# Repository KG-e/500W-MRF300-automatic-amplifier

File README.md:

# 500W-MRF300-automatic-amplifier

A fully automatic 500 W HF amateur radio amplifier (3.5–28 MHz) using a push-pull MRF300 LDMOS output stage with transmission-line transformers (TLTs). The amplifier automatically measures operating frequency, selects the appropriate low-pass filter, adjusts input drive power, monitors protection systems, and includes an automatic antenna tuner and touchscreen HMI.

**Author:** S56KG (https://www.qrz.com/db/S56KG)
This was a final-year high school project (slovenian "tehnična poklicna matura")

---

## Overview

Commercial automatic HF amplifiers with equivalent specs typically cost **3,000–5,000€**. This project was set out to build a comparable **500W HF amplifier** - with automatic band switching, automatic input leveling (attenuator), and full protection circuitry - for half the price (built for ~1,500€ including six output transistors lost to testing mishaps; a second build would cost roughly **1,300€**).

Unlike most homebrew amplifiers, the goal here was full automation: no manual band switching, no manual tuning sequence - just key up and go.

## Key Features

- **Fully automatic operation** - no manual warm-up/tuning procedure required
- **Automatic input attenuator** with power measurement, stepping through 0.5–6 dB stages to hit an ideal ~4W drive level
- **Push-pull output stage** using 2× MRF300 LDMOS transistors, up to ~530W PEP, depending on freq.
- **Automatic low-pass filter selection** based on measured carrier frequency (LPF harmonics are ≤ −65 dBc)
- **Dual-MCU architecture** (2× ATmega2560) communicating over UART, with a custom protocol (type-checked, range-checked, heartbeat-monitored)
- **Nextion touchscreen HMI** showing forward/reflected power, SWR, current, temperature, state, band, gain, and losses in real time
- **Full protection**: overcurrent shutdown (soft-latched via SET-RESET logic), SWR protection, thermal protection, bias monitoring
- **Built-in antenna tuner board** (7x7 L-network, based on the N7DDC ATU-100 topology) - hardware complete, control algorithm in testing
- Extra feature connectors for future interfacing (not yet made PC digital control using a PiPico server) 
- Backup analog voltage/current meter on the front panel

## Design Goals

- At least 450W output
- Fully automatic operation without manual tuning
- Comprehensive protection for the MRF300 output devices 
- Support contest-style rapid TX/RX switching
- Maintain harmonic suppression below −65 dBc
- Operate from 3.5–28 MHz with automatic band detection
- Provide a commercial-style touchscreen HMI for all key operational values
- Build using only readily available components on DigiKey

## How It Works

**Transmit state machine:** `INIT → WAIT → FIRST START → INPUT SETUP → LOW POWER TX → TX SWITCH → HIGH POWER TX → READY`. The "ready" state remembers the last transmission and skips most of the setup sequence on the next key-up for faster switching, useful for competition use.

## Power/SWR Measurement

Power and SWR are measured using a **tandem match coupler**, rather than a simple directional coupler, since directional couplers perform poorly at low freq. HF. Two transformers (current and voltage) are summed/negated to separate forward and reflected power. Each direction feeds an **AD8310** logarithmic RF power detector (for accuracy across a wide dynamic range, from milliwatts to hundreds of watts), digitized by two 16-bit **ADS1115** ADCs over I2C.

## Boards 
| 1 | Attenuator board | Auto input attenuator (relay-switched, 0.5–6 dB stages, 8 stage), input power/SWR meter, built-in 50ohm dummy load 

| 2 | MCU board | Carrier board for ATmega2560 + ATmega16U2 (Arduino Mega-derived); one per controller 

| 3 | Amplifier board | Push-pull 2× MRF300 output stage, TLT output transformers, high-side current sensing, hardware overcurrent latch 

| 4 | Filter board | Output power/SWR metering + auto-selected low-pass filters (designed in AADE Filter Design + LTspice) 

| 5 | Tuner board | 7x7 L-network automatic antenna tuner (hardware complete, not yet enabled) 

| 6 | Motherboard | MCU carrier, per-board regulated supplies, fan control (6× PWM), 2× ADS1115 ADC, buzzer, overcurrent sensing 

| 7 | Input board | RX/TX switching (opto-isolated relay drive), 50V enable, frequency counter 

All boards are 4-layer FR4 (except the tuner board, 2-layer), designed with trace impedance calculated per JLCPCB dielectric specs.

## Firmware

- Two **ATmega2560** microcontrollers, split because driving the Nextion HMI alone slows a single loop to >30ms. This separates time-critical amplifier control from the touchscreen interface to guarantee deterministic protection response.
  - **Primary MCU**: runs the amplifier state machine, controls the amp stage, PSU, RF switching, attenuator, and filters; measures frequency and enforces fast protection (SWR, current, voltage) every loop.
  - **Secondary MCU**: reads temperature/voltage sensors, drives cooling fans, and manages the Nextion HMI.
- Custom UART protocol between the two MCUs with type checking, range validation, and a heartbeat/ID exchange so a reset on either side is detected.
- Faults are split into **soft** (recoverable, resettable from the HMI) and **hard** (critical) — the system is designed so no single fault destroys hardware (in theory, needs more testing to be sure).
- Developed in PlatformIO / VS Code (migrated from Arduino IDE to allow project specific library configuration, needed to change the UART RX buffer without touching global libraries).
- Combined firmware exceeds 3,000 lines across both MCUs.

## HMI

A **Nextion NX4832F035** touchscreen HMI displays input/output power and SWR (with slider gauges), current, temperature, operating state, faults, detected band, gain, and loss — with on-screen soft-fault reset and SSB mode toggle buttons.

## Power Supply

- Toroidal transformer 1200VA and 17V iron core feeding regulated **50V** and **18V** rails respectively, plus soft-start circuitry (needed after an initial testing inrush blew ten smd fuses at once).
- 50V rail: 5x TIP35C NPN transistors (more than strictly needed by current, added for thermal headroom due to insulators).
- 18V rail: 5x LM7818 in a balanced parallel configuration.
- Each PCB has its own local LM78xx/LT1117 regulation on the motherboard to isolate RF noise between stages — important since the amplifier operates on the same frequencies the MCUs use internally.
- Tested at 800W (80% load) for several hours for thermal verification.

## Specifications

| Parameter | Value |
|---|---|
| Output power | 450–500 W (typ.) |
| Accepted drive power | 7–110 W |
| Bands | 3.5, 7, 10, 14, 18, 21, 27 (CB), 28 MHz |
| Gain | > 17 dB (typ.) |
| DC-RF efficiency | ~50% |
| Modes | FM, SSB |
| Harmonics | ≤ −65 dBc |
| Max. antenna SWR | 4:1 |
| Weight | 21.3 kg |
| Dimensions (DxWxH) | 48 × 44 × 20 cm |

## Known Issues

- Occasional spurious fault triggering under unusual operating conditions
- Secondary MCU can fail to start correctly, due to a Nextion library issue that stalls its main loop
- AM modulation is not supported (breaks the frequency counter)
- Reduced output power on the 28 MHz band, due to a suboptimal low-pass filter design in the current revision
- Higher drive power required on 21 MHz and 28 MHz (12W, compared to 7W on 3.5MHz) due to RF detector attenuation characteristics
- The bad 28 MHz LPF has elevated output SWR, degrading output power/SWR readings on that band
- Automatic antenna tuner's hardware is complete but not yet fully tested as the matching algorithm is a difficult mechanism, still under development 
- Lower than desired efficiency of the amp stage, currently about 50%, which pushes power dissipation to the limit
 
This project is shared as inspiration for design ideas, for other homebrew amp builders. I do not recommend attempting to recreate my exact design as there are many subtle details one must account for when building it that you may not know or find unless you are very thorough and understanding of the design.

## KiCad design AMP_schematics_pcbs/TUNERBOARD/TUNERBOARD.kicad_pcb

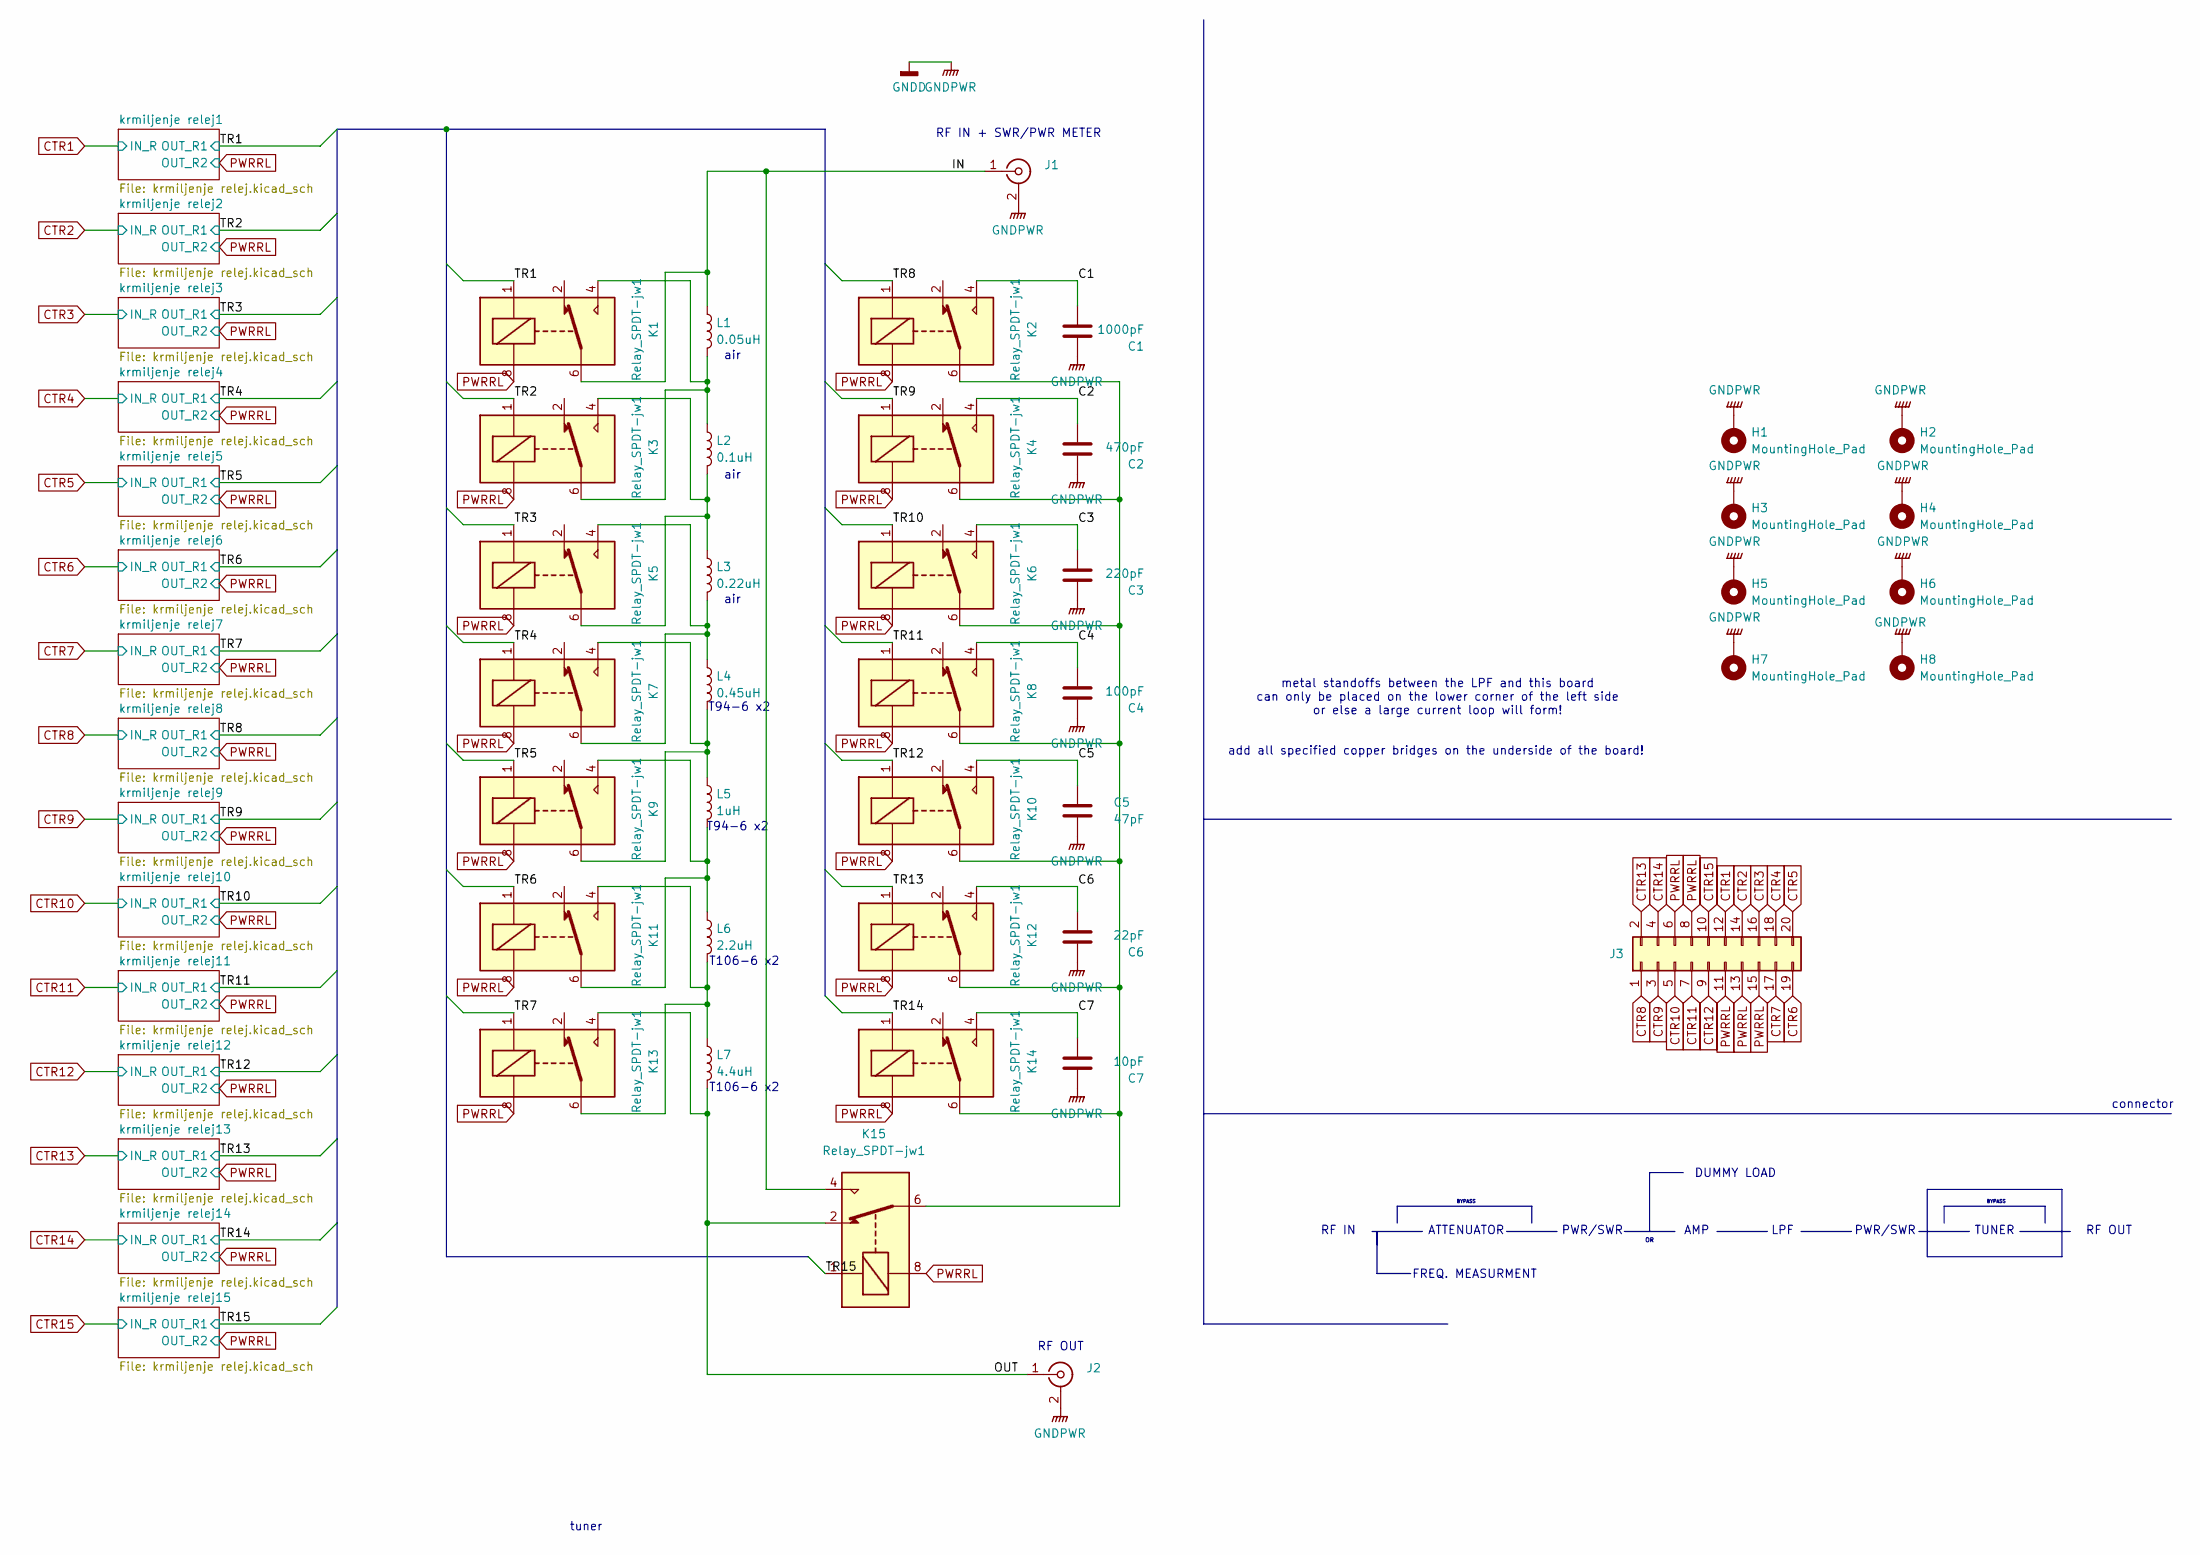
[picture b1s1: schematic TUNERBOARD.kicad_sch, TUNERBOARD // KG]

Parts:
C1: 1000pF; C_1210_3225Metric
C2: 470pF; C_1210_3225Metric
C3: 220pF; C_1210_3225Metric
C4: 100pF; C_1210_3225Metric
C5: 47pF; C_1210_3225Metric
C6: 22pF; C_1210_3225Metric
C7: 10pF; C_1210_3225Metric
H1, H2, H3, H4, H5, H6, H7, H8: MountingHole_Pad; MountingHole_3.2mm_M3_Pad_TopBottom
J1, J2: Conn_Coaxial; SMA_Amphenol_132134_Vertical
J3: Conn_02x10_Odd_Even; PinHeader_2x10_P2.54mm_Vertical
K1, K2, K3, K4, K5, K6, K7, K8, K9, K10, K11, K12, K13, K14, K15: Relay_SPDT-jw1; Relay_premaknjen
L1: 0.05uH; zracnatuljava
L2: 0.1uH; zracnatuljava
L3: 0.22uH; zracnatuljava
L4: 0.45uH; T94-postrani
L5: 1uH; T94-postrani
L6: 2.2uH; T106-lezec
L7: 4.4uH; T106-lezec

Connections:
/C1: C1.2, K2.4
/C2: C2.2, K4.4
/C3: C3.2, K6.4
/C4: C4.2, K8.4
/C5: C5.2, K10.4
/C6: C6.2, K12.4
/C7: C7.2, K14.4
/IN: J1.1 (In), K1.6, K15.4, L1.1
/OUT: J2.1 (In), K13.4, K15.2, L7.2
/TR1: K1.1; also elsewhere on the board
/TR2: K3.1; also elsewhere on the board
/TR3: K5.1; also elsewhere on the board
/TR4: K7.1; also elsewhere on the board
/TR5: K9.1; also elsewhere on the board
/TR6: K11.1; also elsewhere on the board
/TR7: K13.1; also elsewhere on the board
/TR8: K2.1; also elsewhere on the board
/TR9: K4.1; also elsewhere on the board
/TR10: K6.1; also elsewhere on the board
/TR11: K8.1; also elsewhere on the board
/TR12: K10.1; also elsewhere on the board
/TR13: K12.1; also elsewhere on the board
/TR14: K14.1; also elsewhere on the board
/TR15: K15.1; also elsewhere on the board
CTR1: J3.12; also elsewhere on the board
CTR2: J3.14; also elsewhere on the board
CTR3: J3.16; also elsewhere on the board
CTR4: J3.18; also elsewhere on the board
CTR5: J3.20; also elsewhere on the board
CTR6: J3.19; also elsewhere on the board
CTR7: J3.17; also elsewhere on the board
CTR8: J3.1; also elsewhere on the board
CTR9: J3.3; also elsewhere on the board
CTR10: J3.5; also elsewhere on the board
CTR11: J3.7; also elsewhere on the board
CTR12: J3.9; also elsewhere on the board
CTR13: J3.2; also elsewhere on the board
CTR14: J3.4; also elsewhere on the board
CTR15: J3.10; also elsewhere on the board
GNDD: C1.1, C2.1, C3.1, C4.1, C5.1, C6.1, C7.1, H1.1, H2.1, H3.1, H4.1, H5.1, H6.1, H7.1, H8.1, J1.2 (Ext), J2.2 (Ext); also elsewhere on the board
unnamed: K1.4, K3.6, L1.2, L2.1
unnamed: K3.4, K5.6, L2.2, L3.1
unnamed: K5.4, K7.6, L3.2, L4.1
unnamed: K7.4, K9.6, L4.2, L5.1
unnamed: K2.6, K4.6, K6.6, K8.6, K10.6, K12.6, K14.6, K15.6
unnamed: K11.4, K13.6, L6.2, L7.1
unnamed: K9.4, K11.6, L5.2, L6.1
PWRRL: J3.6, J3.8, J3.11, J3.13, J3.15, K1.8, K2.8, K3.8, K4.8, K5.8, K6.8, K7.8, K8.8, K9.8, K10.8, K11.8, K12.8, K13.8, K14.8, K15.8; also elsewhere on the board

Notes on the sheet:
T106-6 x2
ATTENUATOR
add all specified copper bridges on the underside of the board!
DUMMY LOAD
RF OUT
FREQ. MEASURMENT
AMP
LPF
air
PWR/SWR
RF OUT
RF IN + SWR/PWR METER
BYPASS
T94-6 x2
TUNER
RF IN
tuner
metal standoffs between the LPF and this board can only be placed on the lower corner of the left side or else a large current loop will form!
connector

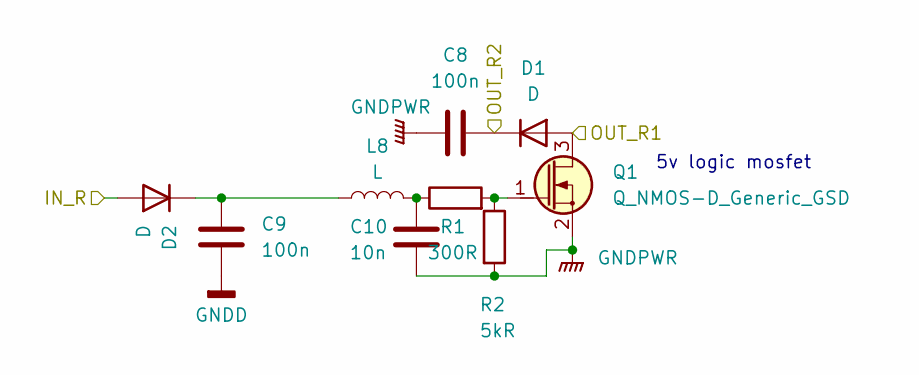
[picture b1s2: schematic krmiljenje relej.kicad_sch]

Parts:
C8, C9: 100n; C_1206_3216Metric_Pad1.33x1.80mm_HandSolder
C10: 10n; C_1206_3216Metric_Pad1.33x1.80mm_HandSolder
D1, D2: D; D_1206_3216Metric_Pad1.42x1.75mm_HandSolder
L8: L; Ferrite_1206_3216Metric_Pad1.42x1.75mm_BigPads
Q1: Q_NMOS-D_Generic_GSD; TSOT-23_HandSoldering
R1: 300R; R_1206_3216Metric_Pad1.30x1.75mm_HandSolder
R2: 5kR; R_1206_3216Metric_Pad1.30x1.75mm_HandSolder

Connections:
/TR1: D1.2 (A), Q1.3 (D); also elsewhere on the board
CTR1: D2.2 (A); also elsewhere on the board
GNDD: C8.2, C9.2, C10.2, Q1.2 (S), R2.2; also elsewhere on the board
unnamed: C10.1, L8.2, R1.1
unnamed: C9.1, D2.1 (K), L8.1
unnamed: Q1.1 (G), R1.2, R2.1
PWRRL: C8.1, D1.1 (K); also elsewhere on the board

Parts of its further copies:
C11, C12, C14, C15, C17, C18, C20, C21, C23, C24, C26, C27, C29, C30, C32, C33, C35, C36, C38, C39, C41, C42, C44, C45, C47, C48, C50, C51: 100n; C_1206_3216Metric_Pad1.33x1.80mm_HandSolder
C13, C16, C19, C22, C25, C28, C31, C34, C37, C40, C43, C46, C49, C52: 10n; C_1206_3216Metric_Pad1.33x1.80mm_HandSolder
D3, D4, D5, D6, D7, D8, D9, D10, D11, D12, D13, D14, D15, D16, D17, D18, D19, D20, D21, D22, D23, D24, D25, D26, D27, D28, D29, D30: D; D_1206_3216Metric_Pad1.42x1.75mm_HandSolder
L9, L10, L11, L12, L13, L14, L15, L16, L17, L18, L19, L20, L21, L22: L; Ferrite_1206_3216Metric_Pad1.42x1.75mm_BigPads
Q2, Q3, Q4, Q5, Q6, Q7, Q8, Q9, Q10, Q11, Q12, Q13, Q14, Q15: Q_NMOS-D_Generic_GSD; TSOT-23_HandSoldering
R3, R5, R7, R9, R11, R13, R15, R17, R19, R21, R23, R25, R27, R29: 300R; R_1206_3216Metric_Pad1.30x1.75mm_HandSolder
R4, R6, R8, R10, R12, R14, R16, R18, R20, R22, R24, R26, R28, R30: 5kR; R_1206_3216Metric_Pad1.30x1.75mm_HandSolder

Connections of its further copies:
/TR2: D3.2 (A), Q2.3 (D); also elsewhere on the board
/TR3: D5.2 (A), Q3.3 (D); also elsewhere on the board
/TR4: D7.2 (A), Q4.3 (D); also elsewhere on the board
/TR5: D9.2 (A), Q5.3 (D); also elsewhere on the board
/TR6: D11.2 (A), Q6.3 (D); also elsewhere on the board
/TR7: D13.2 (A), Q7.3 (D); also elsewhere on the board
/TR8: D15.2 (A), Q8.3 (D); also elsewhere on the board
/TR9: D17.2 (A), Q9.3 (D); also elsewhere on the board
/TR10: D19.2 (A), Q10.3 (D); also elsewhere on the board
/TR11: D21.2 (A), Q11.3 (D); also elsewhere on the board
/TR12: D23.2 (A), Q12.3 (D); also elsewhere on the board
/TR13: D25.2 (A), Q13.3 (D); also elsewhere on the board
/TR14: D27.2 (A), Q14.3 (D); also elsewhere on the board
/TR15: D29.2 (A), Q15.3 (D); also elsewhere on the board
CTR2: D4.2 (A); also elsewhere on the board
CTR3: D6.2 (A); also elsewhere on the board
CTR4: D8.2 (A); also elsewhere on the board
CTR5: D10.2 (A); also elsewhere on the board
CTR6: D12.2 (A); also elsewhere on the board
CTR7: D14.2 (A); also elsewhere on the board
CTR8: D16.2 (A); also elsewhere on the board
CTR9: D18.2 (A); also elsewhere on the board
CTR10: D20.2 (A); also elsewhere on the board
CTR11: D22.2 (A); also elsewhere on the board
CTR12: D24.2 (A); also elsewhere on the board
CTR13: D26.2 (A); also elsewhere on the board
CTR14: D28.2 (A); also elsewhere on the board
CTR15: D30.2 (A); also elsewhere on the board
GNDD: C11.2, C12.2, C13.2, C14.2, C15.2, C16.2, C17.2, C18.2, C19.2, C20.2, C21.2, C22.2, C23.2, C24.2, C25.2, C26.2, C27.2, C28.2, C29.2, C30.2, C31.2, C32.2, C33.2, C34.2, C35.2, C36.2, C37.2, C38.2, C39.2, C40.2, C41.2, C42.2, C43.2, C44.2, C45.2, C46.2, C47.2, C48.2, C49.2, C50.2, C51.2, C52.2, Q2.2 (S), Q3.2 (S), Q4.2 (S), Q5.2 (S), Q6.2 (S), Q7.2 (S), Q8.2 (S), Q9.2 (S), Q10.2 (S), Q11.2 (S), Q12.2 (S), Q13.2 (S), Q14.2 (S), Q15.2 (S), R4.2, R6.2, R8.2, R10.2, R12.2, R14.2, R16.2, R18.2, R20.2, R22.2, R24.2, R26.2, R28.2, R30.2; also elsewhere on the board
unnamed: C13.1, L9.2, R3.1
unnamed: C16.1, L10.2, R5.1
unnamed: C19.1, L11.2, R7.1
unnamed: C22.1, L12.2, R9.1
unnamed: C25.1, L13.2, R11.1
unnamed: C28.1, L14.2, R13.1
unnamed: C31.1, L15.2, R15.1
unnamed: C34.1, L16.2, R17.1
unnamed: C37.1, L17.2, R19.1
unnamed: C40.1, L18.2, R21.1
unnamed: C43.1, L19.2, R23.1
unnamed: C46.1, L20.2, R25.1
unnamed: C49.1, L21.2, R27.1
unnamed: C52.1, L22.2, R29.1
unnamed: C12.1, D4.1 (K), L9.1
unnamed: C15.1, D6.1 (K), L10.1
unnamed: C18.1, D8.1 (K), L11.1
unnamed: C21.1, D10.1 (K), L12.1
unnamed: C24.1, D12.1 (K), L13.1
unnamed: C27.1, D14.1 (K), L14.1
unnamed: C30.1, D16.1 (K), L15.1
unnamed: C33.1, D18.1 (K), L16.1
unnamed: C36.1, D20.1 (K), L17.1
unnamed: C39.1, D22.1 (K), L18.1
unnamed: C42.1, D24.1 (K), L19.1
unnamed: C45.1, D26.1 (K), L20.1
unnamed: C48.1, D28.1 (K), L21.1
unnamed: C51.1, D30.1 (K), L22.1
unnamed: Q2.1 (G), R3.2, R4.1
unnamed: Q3.1 (G), R5.2, R6.1
unnamed: Q4.1 (G), R7.2, R8.1
unnamed: Q5.1 (G), R9.2, R10.1
unnamed: Q6.1 (G), R11.2, R12.1
unnamed: Q7.1 (G), R13.2, R14.1
unnamed: Q8.1 (G), R15.2, R16.1
unnamed: Q9.1 (G), R17.2, R18.1
unnamed: Q10.1 (G), R19.2, R20.1
unnamed: Q11.1 (G), R21.2, R22.1
unnamed: Q12.1 (G), R23.2, R24.1
unnamed: Q13.1 (G), R25.2, R26.1
unnamed: Q14.1 (G), R27.2, R28.1
unnamed: Q15.1 (G), R29.2, R30.1
PWRRL: C11.1, C14.1, C17.1, C20.1, C23.1, C26.1, C29.1, C32.1, C35.1, C38.1, C41.1, C44.1, C47.1, C50.1, D3.1 (K), D5.1 (K), D7.1 (K), D9.1 (K), D11.1 (K), D13.1 (K), D15.1 (K), D17.1 (K), D19.1 (K), D21.1 (K), D23.1 (K), D25.1 (K), D27.1 (K), D29.1 (K); also elsewhere on the board

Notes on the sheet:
5v logic mosfet

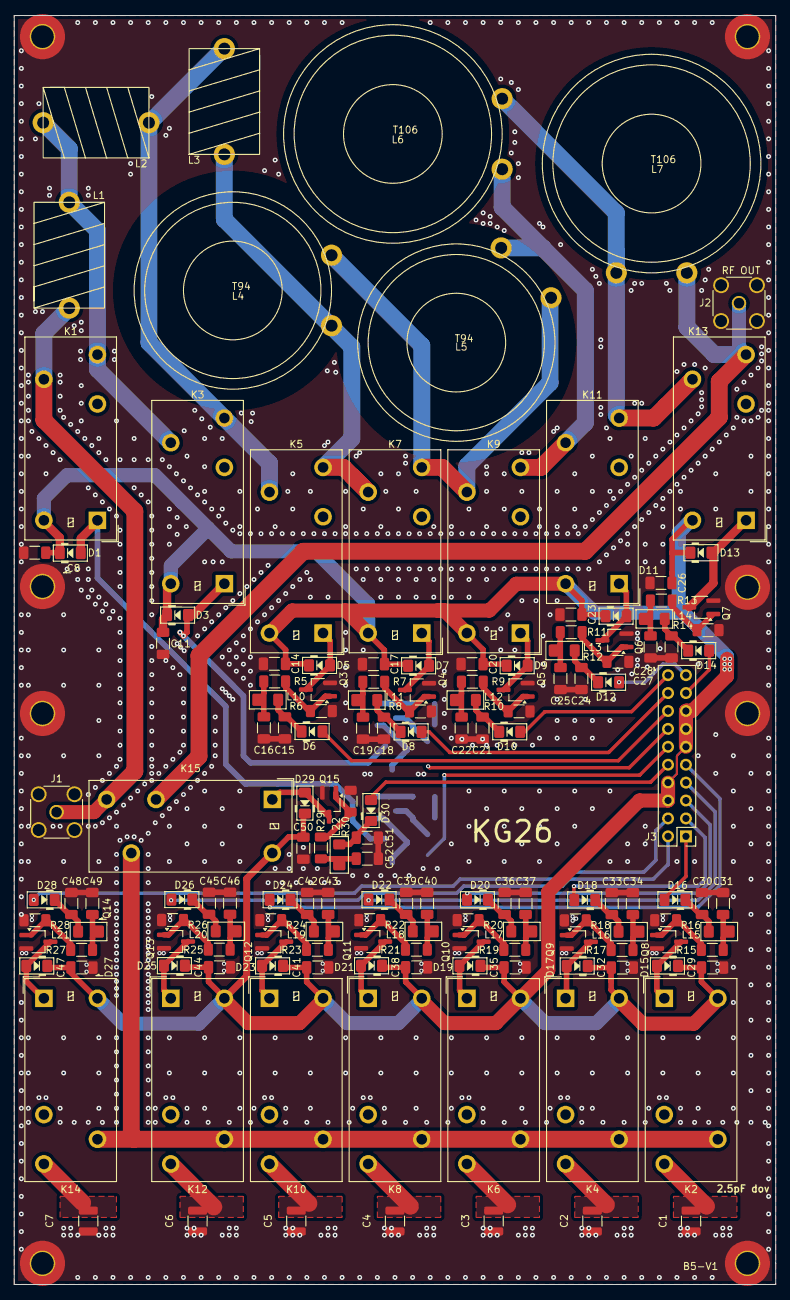
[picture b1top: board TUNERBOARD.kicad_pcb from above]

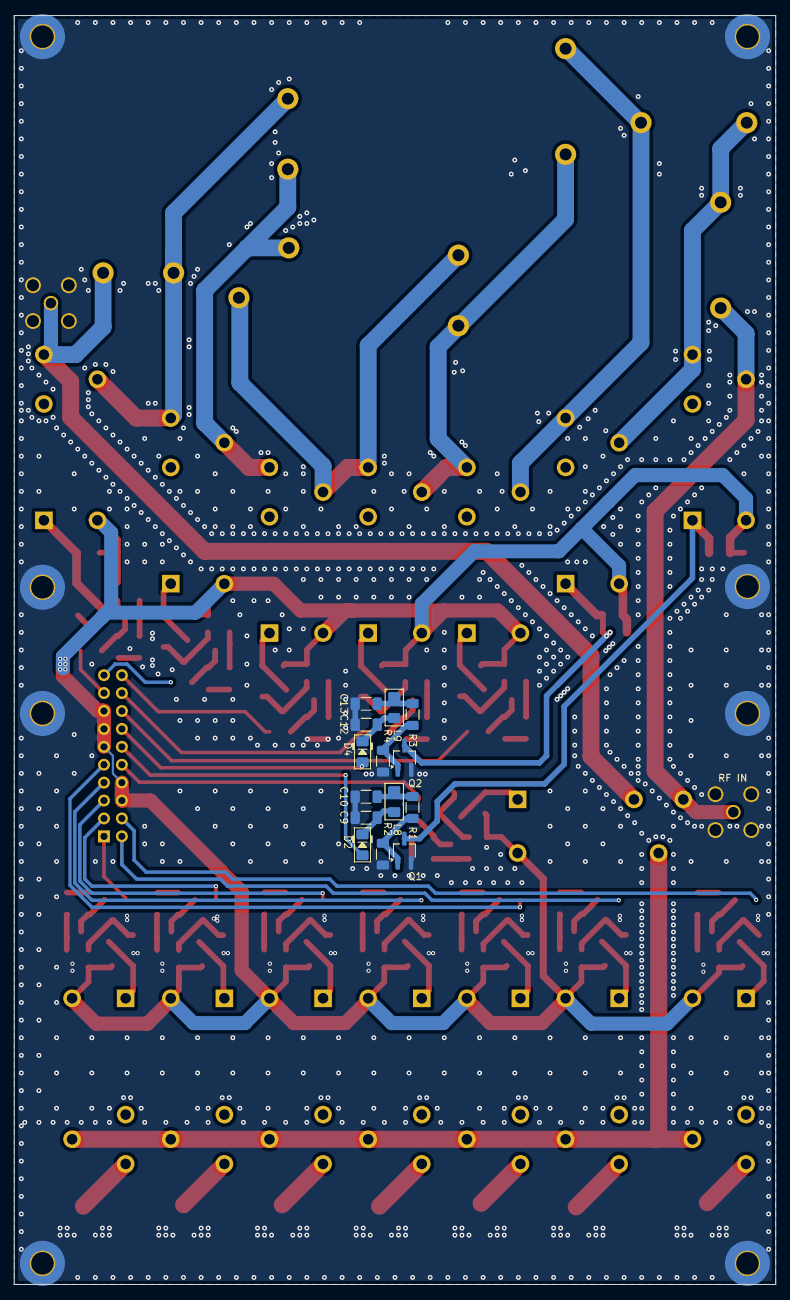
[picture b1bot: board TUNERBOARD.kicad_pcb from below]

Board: 2 copper layers, 108.0 x 180.0 mm, 175 parts (14 on the bottom side), 93 nets.

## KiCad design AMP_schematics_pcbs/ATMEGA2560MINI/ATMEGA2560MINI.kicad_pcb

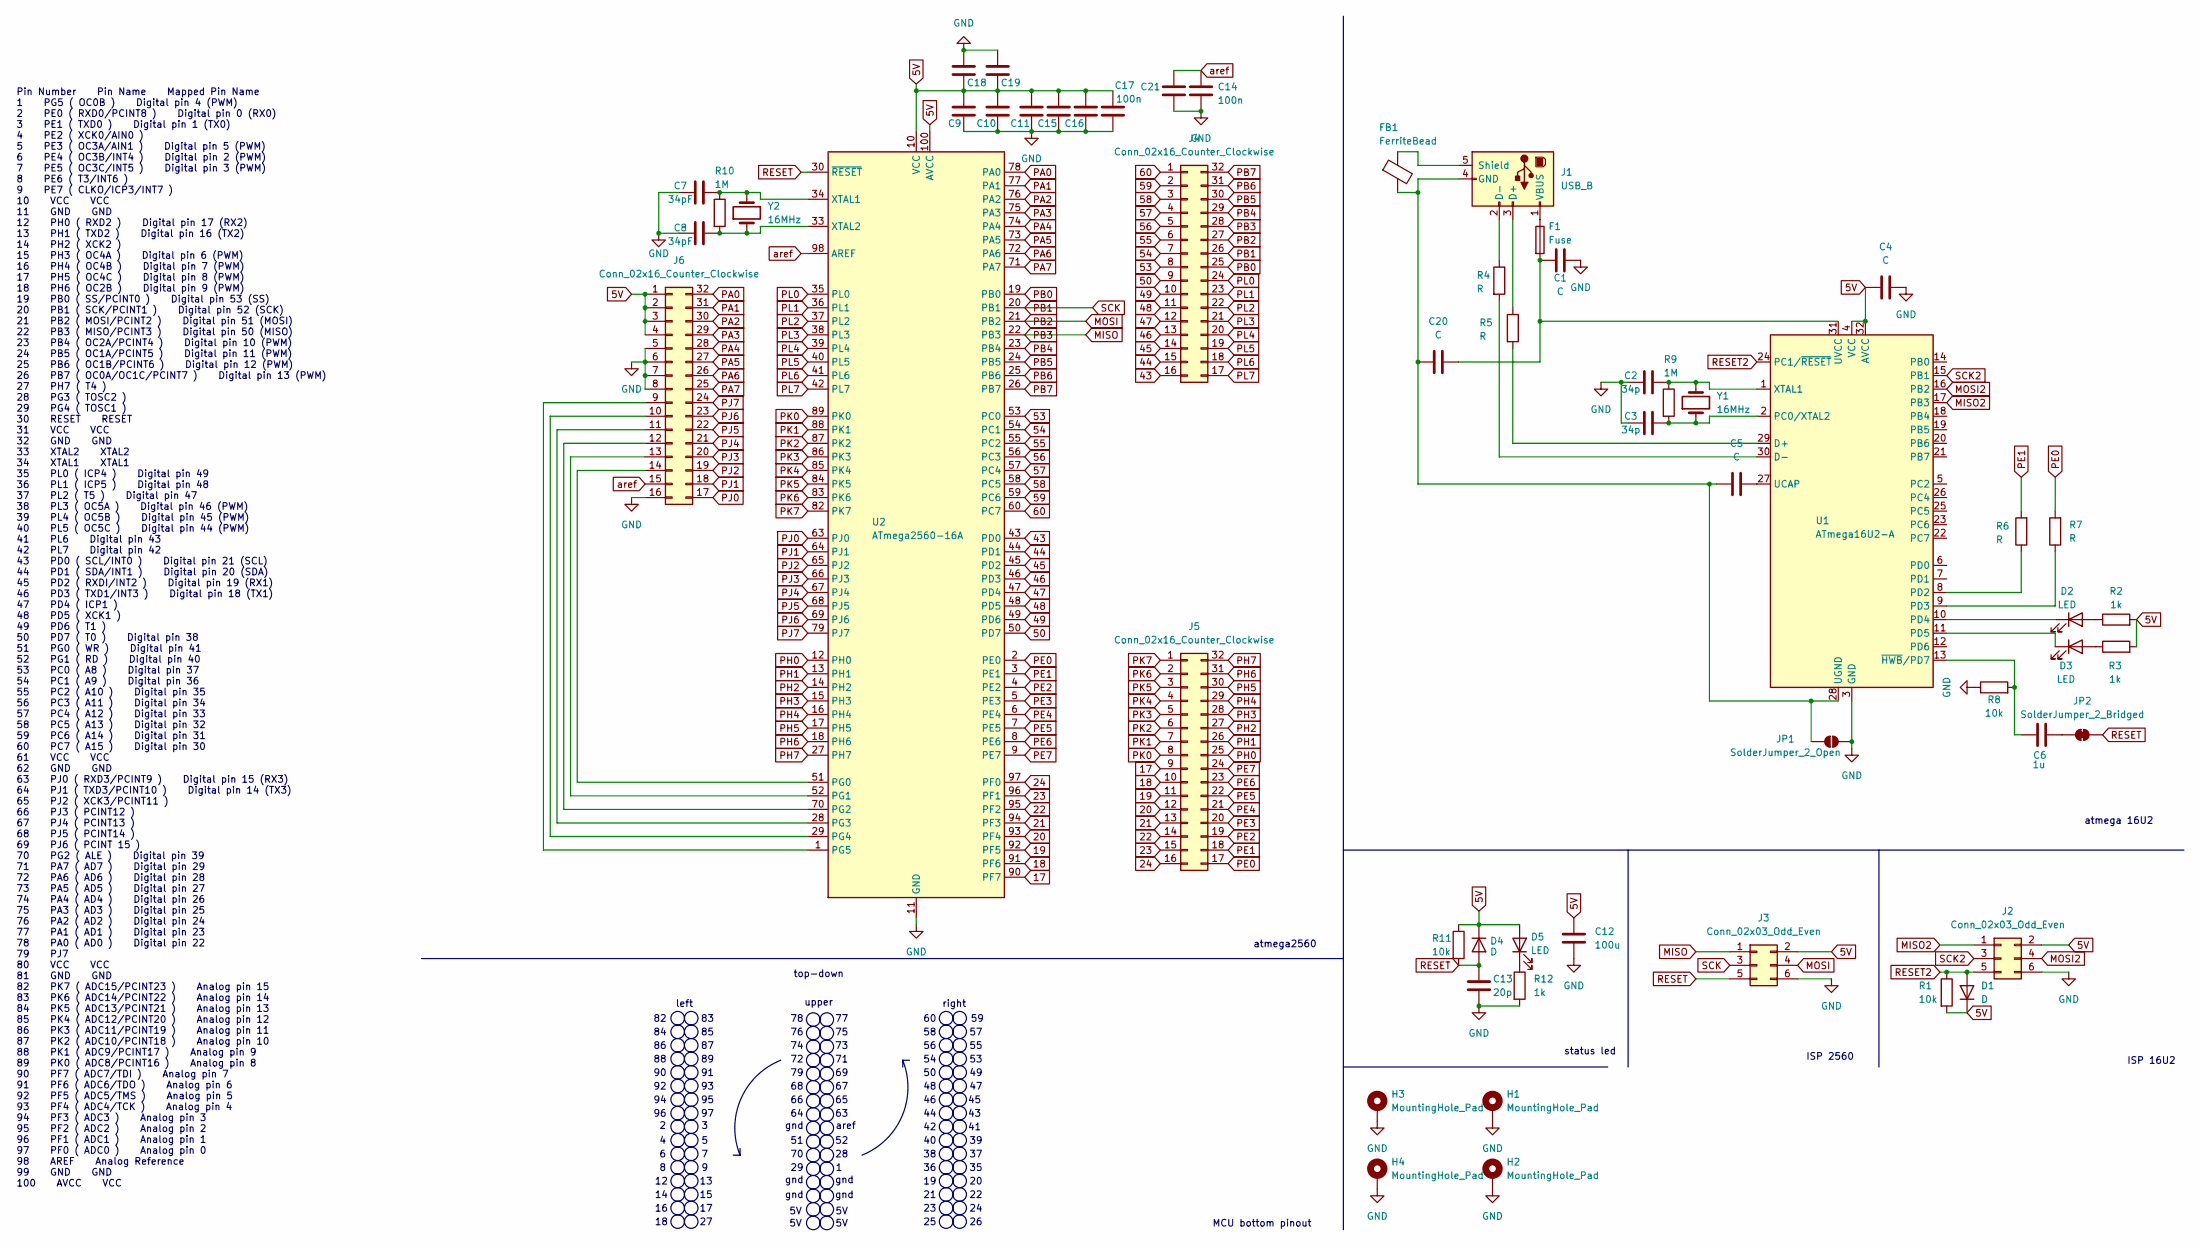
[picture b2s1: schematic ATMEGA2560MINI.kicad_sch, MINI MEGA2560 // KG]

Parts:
C1, C4, C5, C9, C10, C11, C15, C16, C18, C19, C20, C21: C; C_1206_3216Metric_Pad1.33x1.80mm_HandSolder
C2, C3: 34p; C_1206_3216Metric_Pad1.33x1.80mm_HandSolder
C6: 1u; C_1206_3216Metric_Pad1.33x1.80mm_HandSolder
C7, C8: 34pF; C_1206_3216Metric_Pad1.33x1.80mm_HandSolder
C12: 100u; CP_Elec_8x10
C13: 20p; C_1206_3216Metric_Pad1.33x1.80mm_HandSolder
C14, C17: 100n; C_1206_3216Metric_Pad1.33x1.80mm_HandSolder
D1, D4: D; D_1206_3216Metric_Pad1.42x1.75mm_HandSolder
D2, D3, D5: LED; LED_0805_2012Metric_Pad1.15x1.40mm_HandSolder
F1: Fuse; Fuse_1206_3216Metric_Pad1.42x1.75mm_HandSolder
FB1: FerriteBead; L_1806_4516Metric_Pad1.45x1.90mm_HandSolder
H1, H2, H3, H4: MountingHole_Pad; MountingHole_3.2mm_M3_ISO14580_Pad_TopBottom
J1: USB_B; USB_B_TE_5787834_Vertical
J2, J3: Conn_02x03_Odd_Even; PinSocket_2x03_P2.54mm_Vertical
J4, J5, J6: Conn_02x16_Counter_Clockwise; PinHeader_2x16_P2.54mm_Vertical
JP1: SolderJumper_2_Open; SolderJumper-2_P1.3mm_Open_RoundedPad1.0x1.5mm
JP2: SolderJumper_2_Bridged; SolderJumper-2_P1.3mm_Bridged2Bar_RoundedPad1.0x1.5mm
R1, R8, R11: 10k; R_1206_3216Metric_Pad1.30x1.75mm_HandSolder
R2, R3, R12: 1k; R_1206_3216Metric_Pad1.30x1.75mm_HandSolder
R4, R5, R6, R7: R; R_1206_3216Metric_Pad1.30x1.75mm_HandSolder
R9, R10: 1M; R_1206_3216Metric_Pad1.30x1.75mm_HandSolder
U1: ATmega16U2-A; TQFP-32_7x7mm_P0.8mm
U2: ATmega2560-16A; TQFP-100_14x14mm_P0.5mm
Y1, Y2: 16MHz; Crystal_HC49-U_Vertical

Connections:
5V: C4.1, C9.2, C10.2, C11.2, C12.1, C15.2, C16.2, C17.2, C18.2, C19.2, D1.1 (K), D4.1 (K), D5.2 (A), J2.2, J3.2, J6.1, J6.2, J6.3, J6.4, R1.2, R2.2, R3.2, R11.1, U1.4 (VCC), U1.32 (AVCC), U2.10 (VCC), U2.31 (VCC), U2.61 (VCC), U2.80 (VCC), U2.100 (AVCC)
17: J5.9, U2.90 (PF7)
18: J5.10, U2.91 (PF6)
19: J5.11, U2.92 (PF5)
20: J5.12, U2.93 (PF4)
21: J5.13, U2.94 (PF3)
22: J5.14, U2.95 (PF2)
23: J5.15, U2.96 (PF1)
24: J5.16, U2.97 (PF0)
43: J4.16, U2.43 (PD0)
44: J4.15, U2.44 (PD1)
45: J4.14, U2.45 (PD2)
46: J4.13, U2.46 (PD3)
47: J4.12, U2.47 (PD4)
48: J4.11, U2.48 (PD5)
49: J4.10, U2.49 (PD6)
50: J4.9, U2.50 (PD7)
53: J4.8, U2.53 (PC0)
54: J4.7, U2.54 (PC1)
55: J4.6, U2.55 (PC2)
56: J4.5, U2.56 (PC3)
57: J4.4, U2.57 (PC4)
58: J4.3, U2.58 (PC5)
59: J4.2, U2.59 (PC6)
60: J4.1, U2.60 (PC7)
GND: C1.2, C2.1, C3.1, C4.2, C7.1, C8.1, C9.1, C10.1, C11.1, C12.2, C13.2, C14.1, C15.1, C16.1, C17.1, C18.1, C19.1, C21.1, H1.1, H2.1, H3.1, H4.1, J2.6, J3.6, J6.5, J6.6, J6.7, J6.8, J6.16, JP1.2 (B), R8.1, R12.2, U1.3 (GND), U2.11 (GND), U2.32 (GND), U2.62 (GND), U2.81 (GND), U2.99 (GND)
MISO: J3.1, J4.28, U2.22 (PB3)
MISO2: J2.1, U1.17 (PB3)
MOSI: J3.4, J4.27, U2.21 (PB2)
MOSI2: J2.4, U1.16 (PB2)
unnamed: D2.2 (A), R2.1
unnamed: D2.1 (K), U1.10 (PD4)
unnamed: D3.2 (A), R3.1
unnamed: D3.1 (K), U1.11 (PD5)
unnamed: D5.1 (K), R12.1
unnamed: J1.3 (D+), R5.1
unnamed: J1.2 (D-), R4.1
unnamed: C5.1, C20.2, FB1.2, J1.4 (GND), JP1.1 (A), U1.28 (UGND)
unnamed: FB1.1, J1.5 (Shield)
unnamed: F1.1, J1.1 (VBUS)
unnamed: J6.9, U2.1 (PG5)
unnamed: J6.10, U2.29 (PG4)
unnamed: J6.11, U2.28 (PG3)
unnamed: J6.12, U2.70 (PG2)
unnamed: J6.13, U2.52 (PG1)
unnamed: J6.14, U2.51 (PG0)
unnamed: C6.2, JP2.1 (A)
unnamed: R5.2, U1.29 (D+)
unnamed: R4.2, U1.30 (D-)
unnamed: C3.2, R9.2, U1.2 (PC0/XTAL2), Y1.1
unnamed: R6.1, U1.8 (PD2)
unnamed: R7.1, U1.9 (PD3)
unnamed: C5.2, U1.27 (UCAP)
unnamed: C1.1, C20.1, F1.2, U1.31 (UVCC)
unnamed: C2.2, R9.1, U1.1 (XTAL1), Y1.2
unnamed: C6.1, R8.2, U1.13 (~HWB/PD7)
unnamed: C7.2, R10.1, U2.34 (XTAL1), Y2.2
unnamed: C8.2, R10.2, U2.33 (XTAL2), Y2.1
PA0: J6.32, U2.78 (PA0)
PA1: J6.31, U2.77 (PA1)
PA2: J6.30, U2.76 (PA2)
PA3: J6.29, U2.75 (PA3)
PA4: J6.28, U2.74 (PA4)
PA5: J6.27, U2.73 (PA5)
PA6: J6.26, U2.72 (PA6)
PA7: J6.25, U2.71 (PA7)
PB0: J4.25, U2.19 (PB0)
PB1: J3.3, J4.26, U2.20 (PB1)
PB4: J4.29, U2.23 (PB4)
PB5: J4.30, U2.24 (PB5)
PB6: J4.31, U2.25 (PB6)
PB7: J4.32, U2.26 (PB7)
PE0: J5.17, R7.2, U2.2 (PE0)
PE1: J5.18, R6.2, U2.3 (PE1)
PE2: J5.19, U2.4 (PE2)
PE3: J5.20, U2.5 (PE3)
PE4: J5.21, U2.6 (PE4)
PE5: J5.22, U2.7 (PE5)
PE6: J5.23, U2.8 (PE6)
PE7: J5.24, U2.9 (PE7)
PH0: J5.25, U2.12 (PH0)
PH1: J5.26, U2.13 (PH1)
PH2: J5.27, U2.14 (PH2)
PH3: J5.28, U2.15 (PH3)
PH4: J5.29, U2.16 (PH4)
PH5: J5.30, U2.17 (PH5)
PH6: J5.31, U2.18 (PH6)
PH7: J5.32, U2.27 (PH7)
PJ0: J6.17, U2.63 (PJ0)
PJ1: J6.18, U2.64 (PJ1)
PJ2: J6.19, U2.65 (PJ2)
PJ3: J6.20, U2.66 (PJ3)
PJ4: J6.21, U2.67 (PJ4)
PJ5: J6.22, U2.68 (PJ5)
PJ6: J6.23, U2.69 (PJ6)
PJ7: J6.24, U2.79 (PJ7)
PK0: J5.8, U2.89 (PK0)
PK1: J5.7, U2.88 (PK1)
PK2: J5.6, U2.87 (PK2)
PK3: J5.5, U2.86 (PK3)
PK4: J5.4, U2.85 (PK4)
PK5: J5.3, U2.84 (PK5)
PK6: J5.2, U2.83 (PK6)
PK7: J5.1, U2.82 (PK7)
PL0: J4.24, U2.35 (PL0)
PL1: J4.23, U2.36 (PL1)
PL2: J4.22, U2.37 (PL2)
PL3: J4.21, U2.38 (PL3)
PL4: J4.20, U2.39 (PL4)
PL5: J4.19, U2.40 (PL5)
PL6: J4.18, U2.41 (PL6)
PL7: J4.17, U2.42 (PL7)
RESET: C13.1, D4.2 (A), J3.5, JP2.2 (B), R11.2, U2.30 (~RESET)
RESET2: D1.2 (A), J2.5, R1.1, U1.24 (PC1/~RESET)
SCK2: J2.3, U1.15 (PB1)
aref: C14.2, C21.2, J6.15, U2.98 (AREF)

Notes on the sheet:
aref
gnd
status led
top-down
atmega2560
atmega 16U2
right
ISP 16U2
ISP 2560
upper
MCU bottom pinout
Pin Number Pin Name Mapped Pin Name 1 PG5 ( OC0B ) Digital pin 4 (PWM) 2 PE0 ( RXD0/PCINT8 ) Digital pin 0 (RX0) 3 PE1 ( TXD0 ) Digital pin 1 (TX0) 4 PE2 ( XCK0/AIN0 ) 5 PE3 ( OC3A/AIN1 ) Digital pin 5 (PWM) 6 PE4 ( OC3B/INT4 ) Digital pin 2 (PWM) 7 PE5 ( OC3C/INT5 ) Digital pin 3 (PWM) 8 PE6 ( T3/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
left

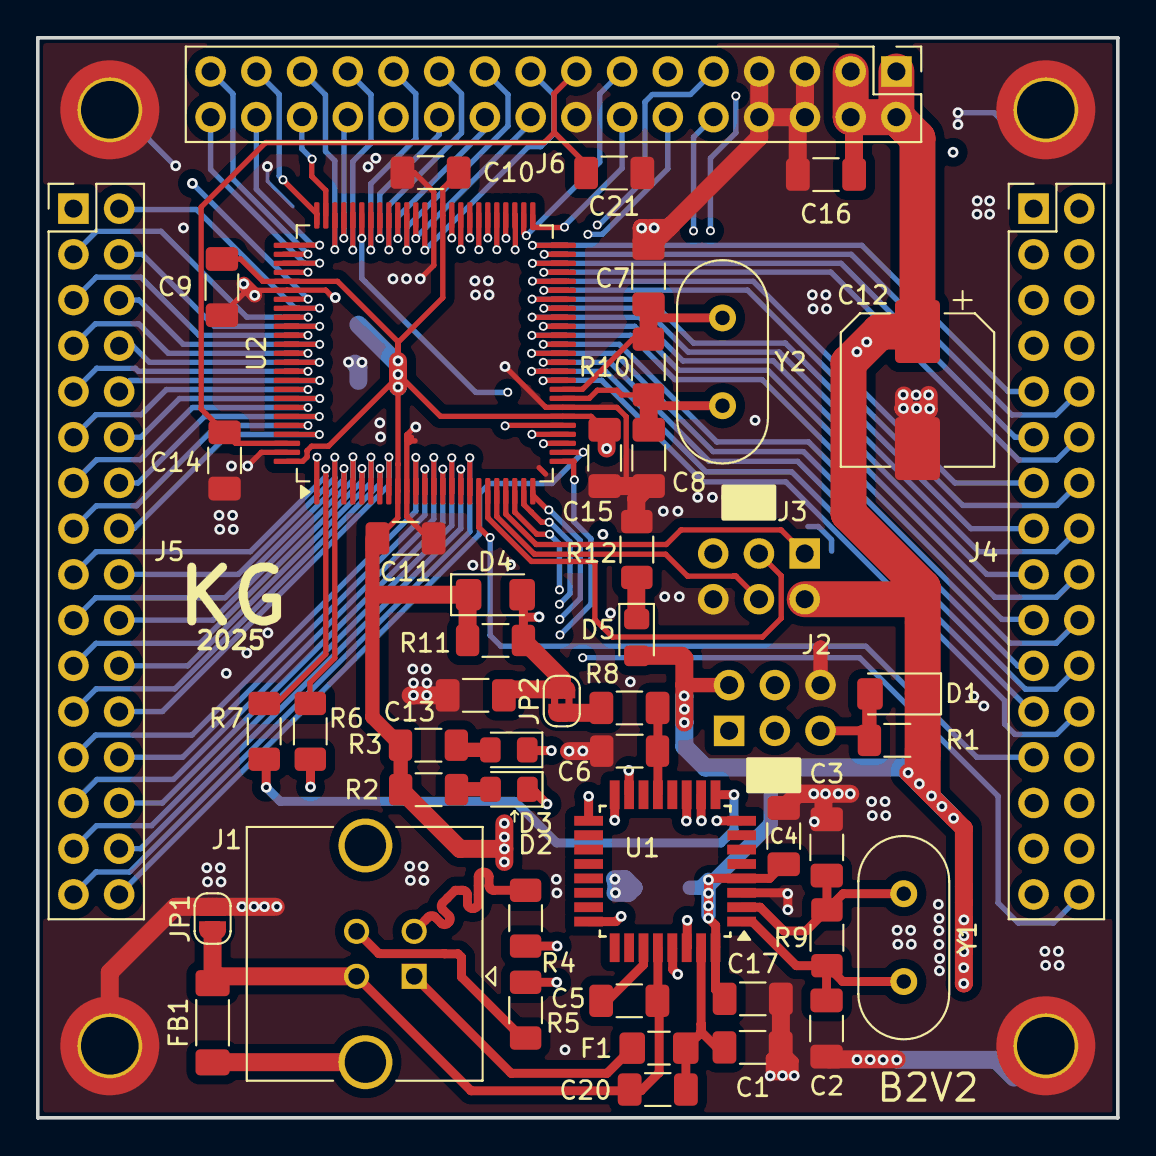
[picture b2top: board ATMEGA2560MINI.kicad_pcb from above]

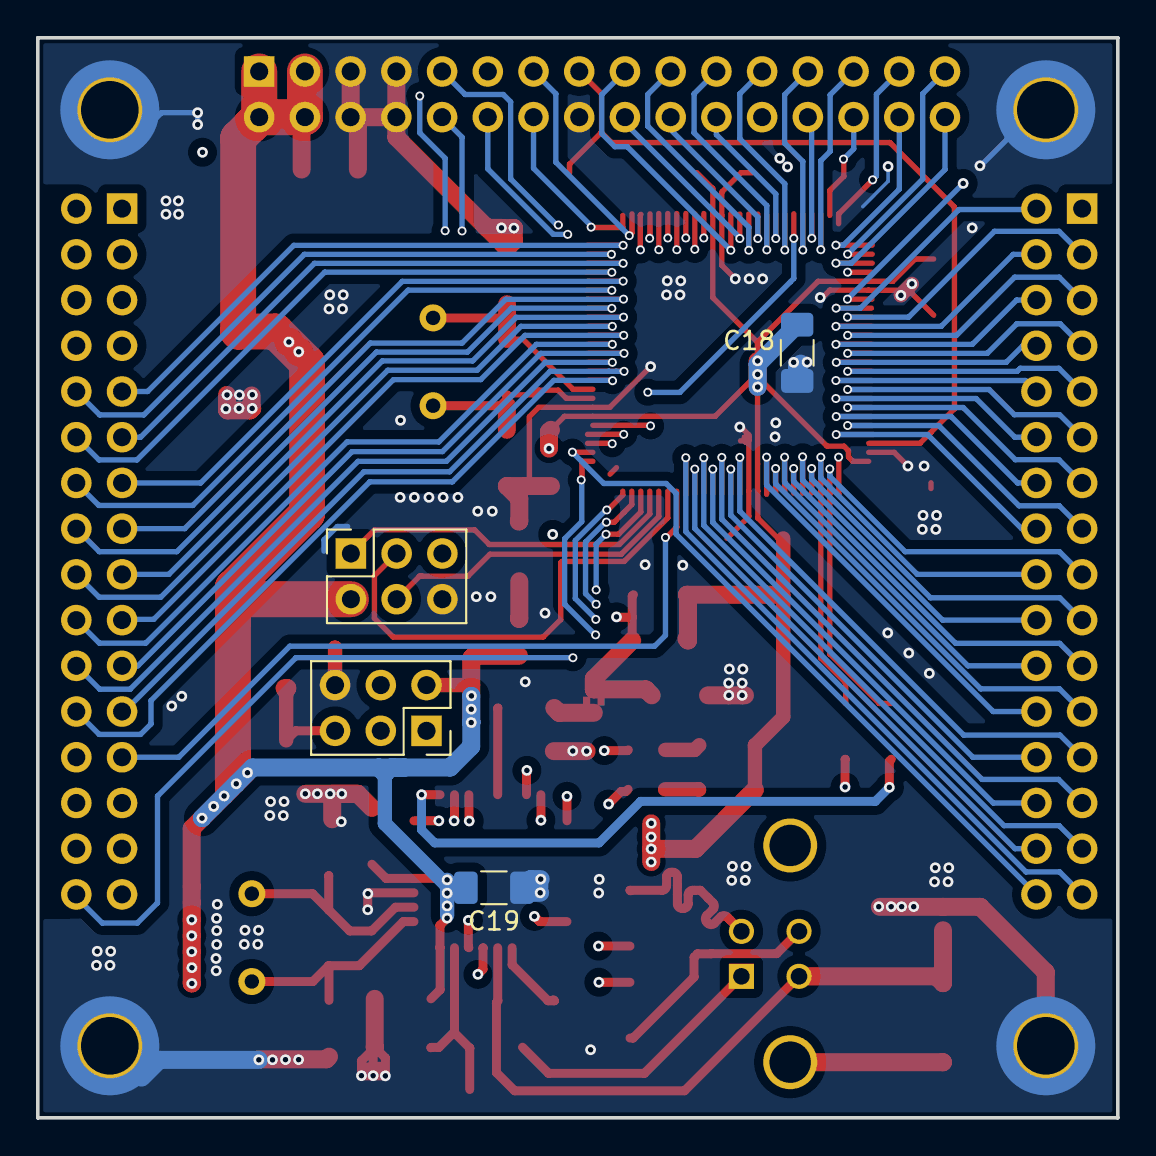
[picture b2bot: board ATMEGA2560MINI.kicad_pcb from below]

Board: 4 copper layers, 60.0 x 60.0 mm, 56 parts (4 on the bottom side), 116 nets.
